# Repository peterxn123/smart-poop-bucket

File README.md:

# smart-poop-bucket

Physical build:

Smart 3D printer poop bucket suitable for the Bambu A1. Track your poop with the web interface. Uses a Xiao ESP32-S3, HX711 and a 50kg load cell. This very handy tool makes it easier to manage your (printer) poop, by allowing you to monitor live your poop grammage for each print. As I'm sure you know, the slicer's estimate is only just that - an estimate - and so when it is important to know the total filament usage, for example when calculating the cost of a 3D print to sell, this handy tool allows you to see the exact weight of poop output by the printer per print. Uses the public HX711 micropython lib, so this project is therefore shared under an MIT license.

Why did I create this? Well, simply put, I hate the waste produced by multicolour prints. I like to minimise my waste when printing, and also when I sell my multicolour prints I need to calculate the price by including the weight of the poop and the printed objects. So, I thought it would be really handy, rather than me having to empty my poop bin and weigh it myself every time, instead have a smart poop bin where I can keep track of the poop weight of each print, without having to go through the hassle of weighing it myself. This should make selling 3D prints easier for anyone who uses the AMS lite system with their A1.

**The poop bucket itself, with the minecraft chest theme:**

**The PCB:**

**The base which houses the electronics and weigh scales - the chest goes on top of this**

**Bottom side of the base:**

**The chest and the base together:**

```

Wiring diagram:

             ┌──────────────────────────────────────────────┐
             │                 Generic ESP32-S3             │
             │                                              │
             │ GPIO16 ────────► DT (HX711)                  │
             │ GPIO17 ────────► SCK (HX711)                 │
             │ 3V3   ────────► VCC (HX711)                  │
             │ GND   ────────► GND (HX711)                  │
             └──────────────────────────────────────────────┘

             ┌──────────────────────────────────────────────┐
             │                  HX711 Module                │
             │                                              │
             │ VCC   ◄─────── 3V3 (ESP32-S3)                │
             │ GND   ◄─────── GND (ESP32-S3)                │
             │ DT    ◄─────── GPIO4 (ESP32-S3)              │
             │ SCK   ◄─────── GPIO5 (ESP32-S3)              │
             │ E+    ◄─────── Red wire (Load Cell)          │
             │ E-    ◄─────── Black wire (Load Cell)        │
             │ A-    ◄─────── White wire (Load Cell)        │
             └──────────────────────────────────────────────┘

             ┌──────────────────────────────────────────────┐
             │                50kg Load Cell                │
             │                                              │
             │ Red   ───────► E+ (HX711)                    │
             │ Black ───────► E- (HX711)                    │
             │ White ───────► A- (HX711)                    │
             └──────────────────────────────────────────────┘

```

BOM:

| Quantity | Component                    | Model / Description                                      | Purchase Link                                                                                                                        | Cost (GBP) |
|----------|------------------------------|----------------------------------------------------------|----------------------------------------------------------------------------------------------------------------------------------------|------------|
| 1        | Xiao ESP32-S3                | Xiao ESP32-S3 devboard                                   | [Link to ESP32-S3](https://www.aliexpress.com/item/1005007426784408.html?spm=a2g0o.productlist.main.1.28895274bF7p0T)                  | £9.19      |
| 1        | HX711 Load Cell Amplifier + 50KG | HX711 24-bit ADC module bundled with 50kg load cells | [Link to HX711 Load Cell](https://www.amazon.co.uk/Weighting-Half-bridge-Amplifier-Bathroom-Arduino/dp/B07FMN1DBN/ref=sr_1_45)         | £7.98      |
| 40       | Jumper Wires (male–female)   | Dupont jumper wires set                                  | [Link to Jumper Wires](https://www.amazon.co.uk/40pcs-Dupont-Female-Jumper-Connectors/dp/B013EW65H2/ref=sr_1_28)                       | £3.99      |
| 1        | Custom PCB                   | JLCPCB fabricated PCB                                    | [JLCPCB](https://jlcpcb.com)                                                                                                            | £1.57 ($2)     |
|          |                              |                                                          |                                                                                                                                        | **£22.73** |

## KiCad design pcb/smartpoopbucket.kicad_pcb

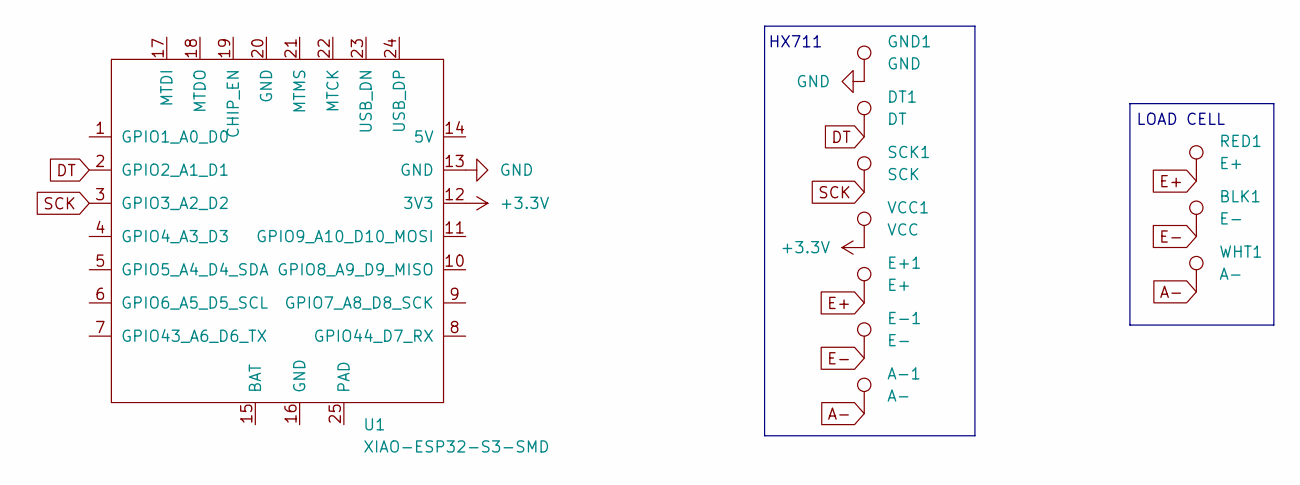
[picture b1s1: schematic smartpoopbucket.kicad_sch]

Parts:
A-1: A-; SolderWirePad_1x01_SMD_1x2mm
BLK1: E-; SolderWirePad_1x01_SMD_1x2mm
DT1: DT; SolderWirePad_1x01_SMD_1x2mm
E+1: E+; SolderWirePad_1x01_SMD_1x2mm
E-1: E-; SolderWirePad_1x01_SMD_1x2mm
GND1: GND; SolderWirePad_1x01_SMD_1x2mm
RED1: E+; SolderWirePad_1x01_SMD_1x2mm
SCK1: SCK; SolderWirePad_1x01_SMD_1x2mm
U1: XIAO-ESP32-S3-SMD; XIAO-ESP32S3-SMD
VCC1: VCC; SolderWirePad_1x01_SMD_1x2mm
WHT1: A-; SolderWirePad_1x01_SMD_1x2mm

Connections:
+3.3V: U1.12 (3V3), VCC1.1
A-: A-1.1, WHT1.1
DT: DT1.1, U1.2 (GPIO2_A1_D1)
E+: E+1.1, RED1.1
E-: BLK1.1, E-1.1
GND: GND1.1, U1.13 (GND)
SCK: SCK1.1, U1.3 (GPIO3_A2_D2)

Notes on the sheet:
LOAD CELL
HX711

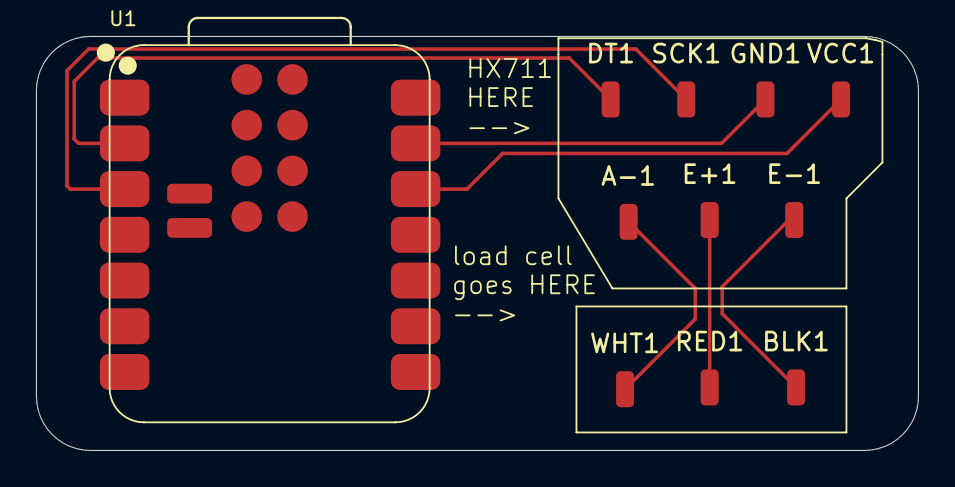
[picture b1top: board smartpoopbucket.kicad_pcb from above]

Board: 2 copper layers, 49.0 x 23.0 mm, 11 parts (0 on the bottom side), 7 nets.

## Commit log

2025-08-01 add BOM
2025-08-01 add CAD
2025-08-01 Add firmware
2025-08-01 Added the lib files for the hx711
2025-08-06 Add PCB files
2025-08-06 Replaced old CAD with new upgraded CAD of the chest.
2025-08-23 Updated CAD and firmware
2025-08-23 Updated main firmware`
2025-08-27 Updated journal
2025-09-21 Update journal
2025-09-21 Add new images
    Add new more detailed images of the physical build
